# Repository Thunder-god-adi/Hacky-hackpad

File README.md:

# Hackpad
Yo Boizzz , This Is A MACROPAD That Includes 6 Keys [Mechanical] with 4x EC11 Rotary Encoders And 1x OLED Diplay...

# FEATURES 
1->> Full Of Functionable Keys 6 </n>

2->> Rotary Encoders { Cool Scrolllss }</n>

3->> Fully Customizable { Modify The Code For Ur Own Functioning }</n>

# IMAGESSS

# Bill of Materials (BOM)
| Name                 | Specification              | Cost (USD) | Qty | Total (USD) | Distributor | Links
| -------------------- | -------------------------- | ---------- | --- | ----------- | ----------- | -------------
| PCB                  | Custom macropad (5x4)      | $11.00     | 5   | $11.00      | JLCPCB      |
| XIAO                 | Microcontroller            | $7.00      | 1   | $7.00       | Seeed       |https://robocraze.com/products/seeed-studio-xiao-rp2040-development-board?variant=47742255562976&country=IN&currency=INR&utm_medium=product_sync&utm_source=google&utm_content=sag_organic&utm_campaign=sag_organic&campaignid=23145906364&adgroupid=182236965810&keyword=&device=c&gad_source=1&gad_campaignid=23145906364&gbraid=0AAAAADgHQvYUeFOurHuv6PLSnvMBwnIzx&gclid=EAIaIQobChMI_72N3ZGRlQMVCm0PAh03gDIyEAQYASABEgKj0_D_BwE
| OLED Display         | Display Module             | $2.00      | 1   | $2.00       | Amazon      |https://robu.in/product/blue-oled-display-module/?gad_source=1&gad_campaignid=17416544847&gbraid=0AAAAADvLFWdzc52j7dV6p7wFeXCaHnsev&gclid=EAIaIQobChMIyqv4u5WRlQMV56xmAh27RQj0EAQYASABEgLAIvD_BwE
| EC11 Rotary Encoder  | EC11 10K Rotary Encoder    | $3.00      | 1   | $3.00       | Amazon      |https://www.amazon.in/CentIoT%C2%AE-Encoder-Digital-Potentiometer-Control/dp/B07THRXT4F?th=1
| Keycaps              | Keycaps Set                | $5.00      | 1   | $5.00       | amazon      |https://www.amazon.in/CALANDISTM-Transparent-Switches-Keyboards-Pointers/dp/B0F13YK4D6/ref=sr_1_15?crid=31R4WY38LW94N&dib=eyJ2IjoiMSJ9.fc7HUd79C10vfF_Eyd2mjm8NtqMOcMUS9WgGvXSTZvFp0zT8GSnqhjNSi-y0B3FQef1s2rCsyGH694M5ZMllZ6cMyfb3ZhJv4H3klhO1ot4O26EqJN127DB4ECZB-V5KF-wWUdNZVPs3dqjiy1CkJ-RC1QNJOaZLdW6Y8FieVq5TENI7_deSUReVvdkdj0WA01Xp_64MSrOE512448V-cYtIaGjS3rqsqeiznWHe7ic.h9hxENgx5ndPqOtUe5idjH_anbYI0x7-MfRV3lBG5Vo&dib_tag=se&keywords=keycaps&qid=1781798827&sprefix=keycaps%2Caps%2C271&sr=8-15
| Mechanical Switches  | Mechanical Keyboard Switch | $4.00      | 1   | $4.00       | Amazon      |https://www.amazon.in/Mechanical-Dustproof-Hot-Swappable-Compatible-Keyboards/dp/B0FPR2ML31?source=ps-sl-shoppingads-lpcontext&ref_=fplfs&psc=1&smid=A16FKXBMFHBYH0
| **TOTAL**            |                            |            |     | **$32.00**  |             |
## JLCPCB

**IDK WHY EVERYTHING IS SO EXPENSIVE IN INDIA**

**Total Estimated Cost**: `$5 WITH SHIPPING CHARGES INCLUDED`
I'm only asking for pcb cost as you guys said.

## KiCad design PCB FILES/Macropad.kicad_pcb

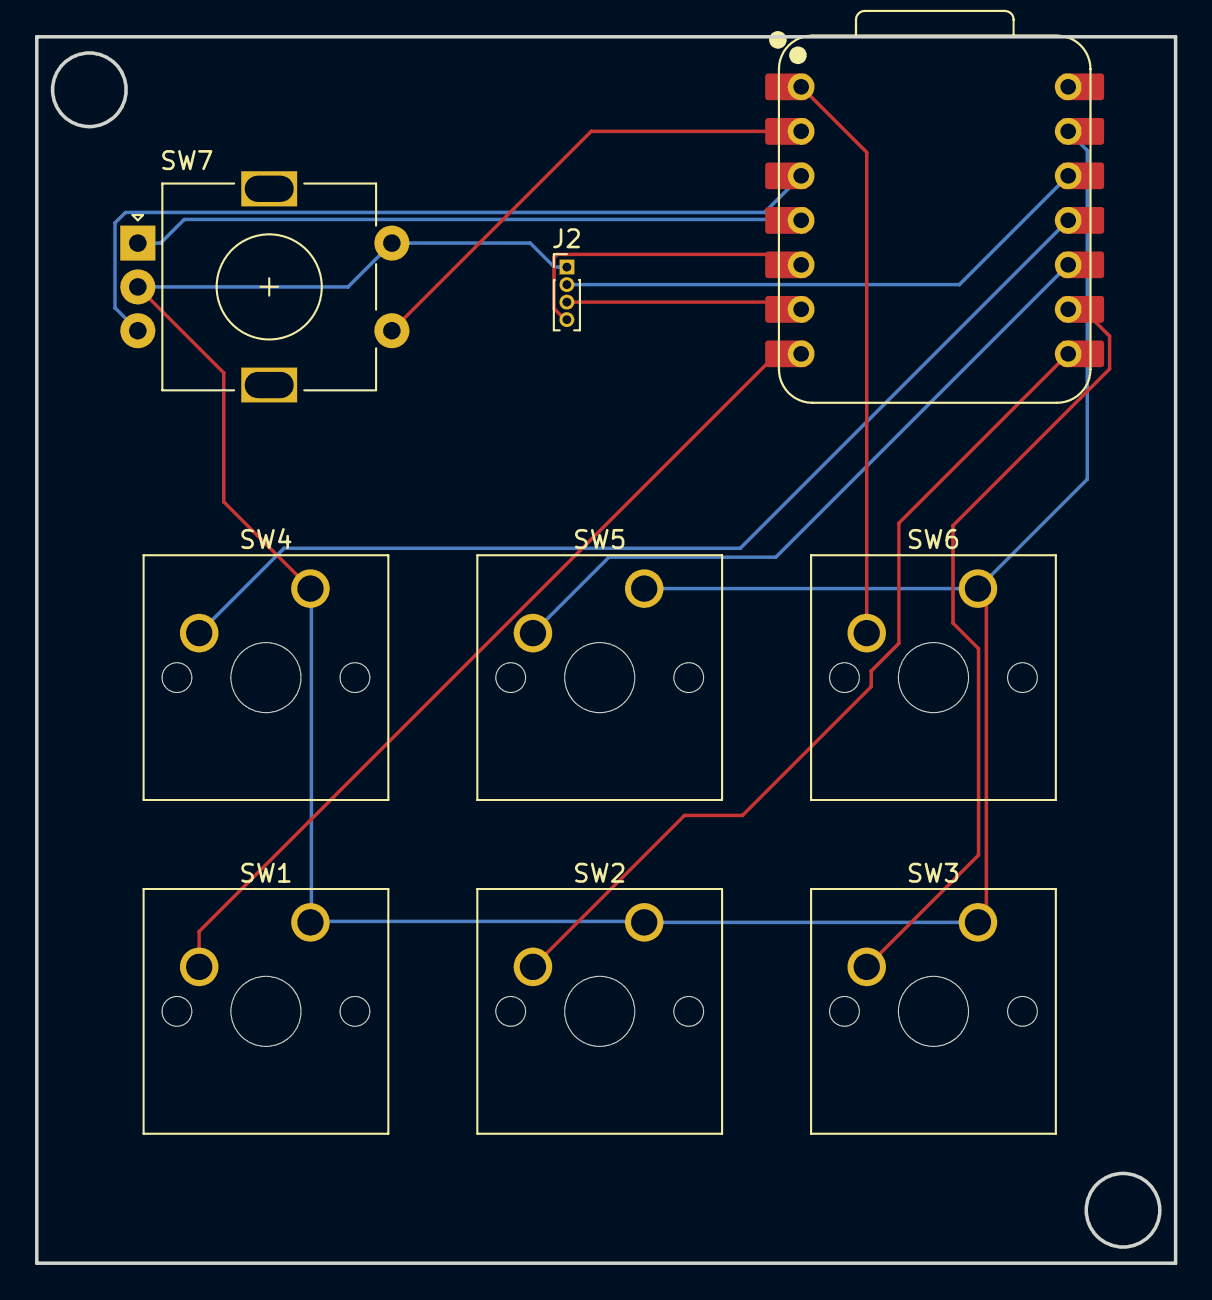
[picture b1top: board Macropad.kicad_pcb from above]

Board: 2 copper layers, 65.0 x 70.0 mm, 9 parts (0 on the bottom side), 13 nets.

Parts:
J2: Conn_01x04_Pin; PinHeader_1x04_P1.00mm_Vertical
SW1, SW2, SW3, SW4, SW5, SW6: SW_Push; SW_Cherry_MX_1.00u_PCB
SW7: RotaryEncoder_Switch; RotaryEncoder_Alps_EC11E-Switch_Vertical_H20mm
U1: XIAO-RP2040-DIP

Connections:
GND: J2.1, SW1.1, SW2.1, SW3.1, SW4.1, SW5.1, SW6.1, SW7.C, SW7.S2, U1.13 (GND)
S1: SW7.S1, U1.2 (GPIO27/ADC1/A1)
SCL: J2.3, U1.6 (GPIO7/SCL)
SDA: J2.4, U1.5 (GPIO6/SDA)
SW1: SW1.2, U1.7 (GPIO0/TX)
SW2: SW2.2, U1.8 (GPIO1/RX)
SW3: SW3.2, U1.9 (GPIO2/SCK)
SW4: SW4.2, U1.11 (GPIO3/MOSI)
SW5: SW5.2, U1.10 (GPIO4/MISO)
SW6: SW6.2, U1.1 (GPIO26/ADC0/A0)
SWA: SW7.A, U1.4 (GPIO29/ADC3/A3)
SWB: SW7.B, U1.3 (GPIO28/ADC2/A2)
VCC: J2.2, U1.12 (3V3)
